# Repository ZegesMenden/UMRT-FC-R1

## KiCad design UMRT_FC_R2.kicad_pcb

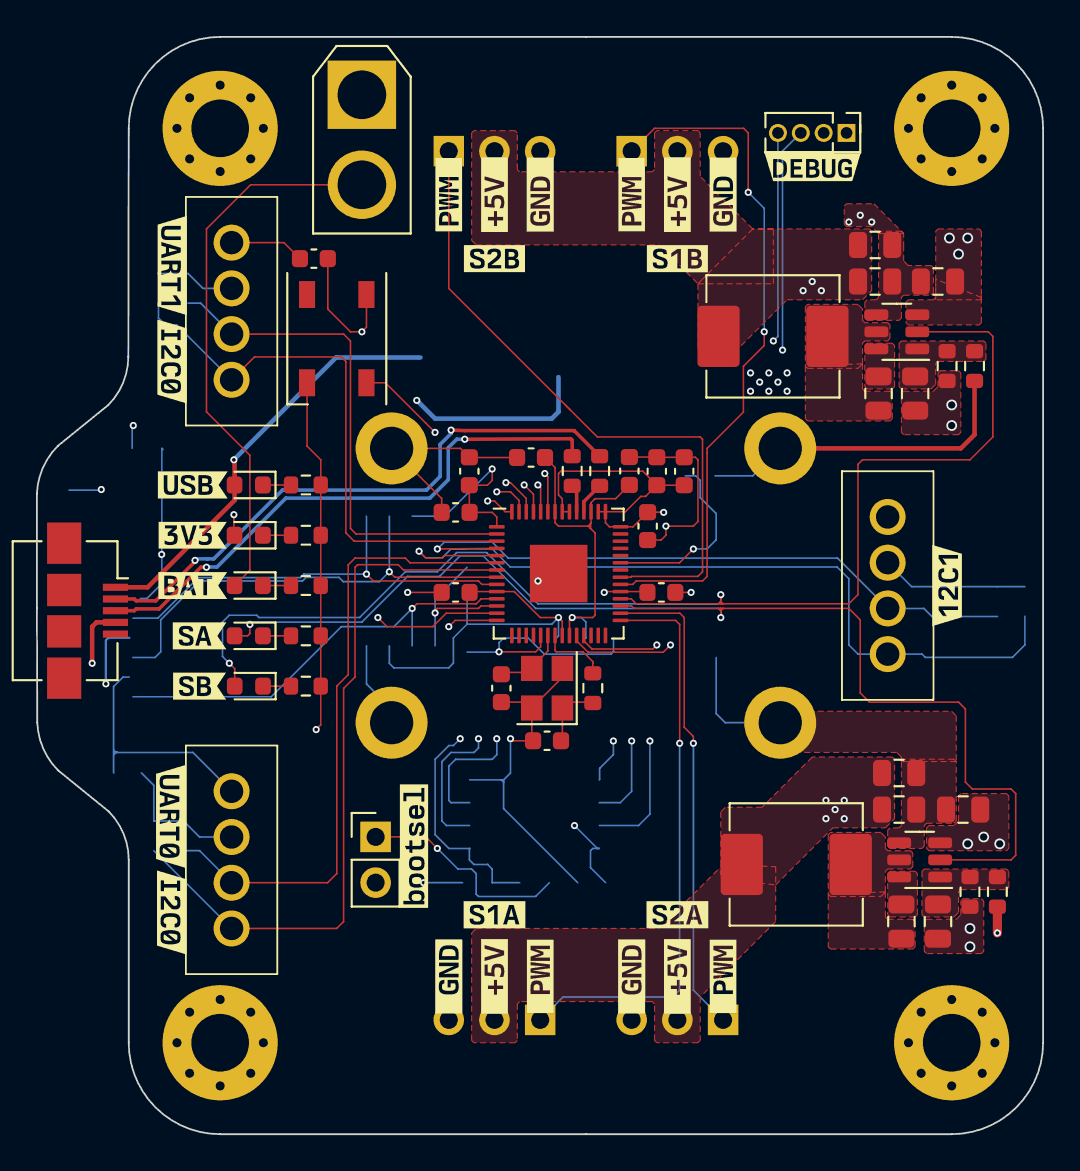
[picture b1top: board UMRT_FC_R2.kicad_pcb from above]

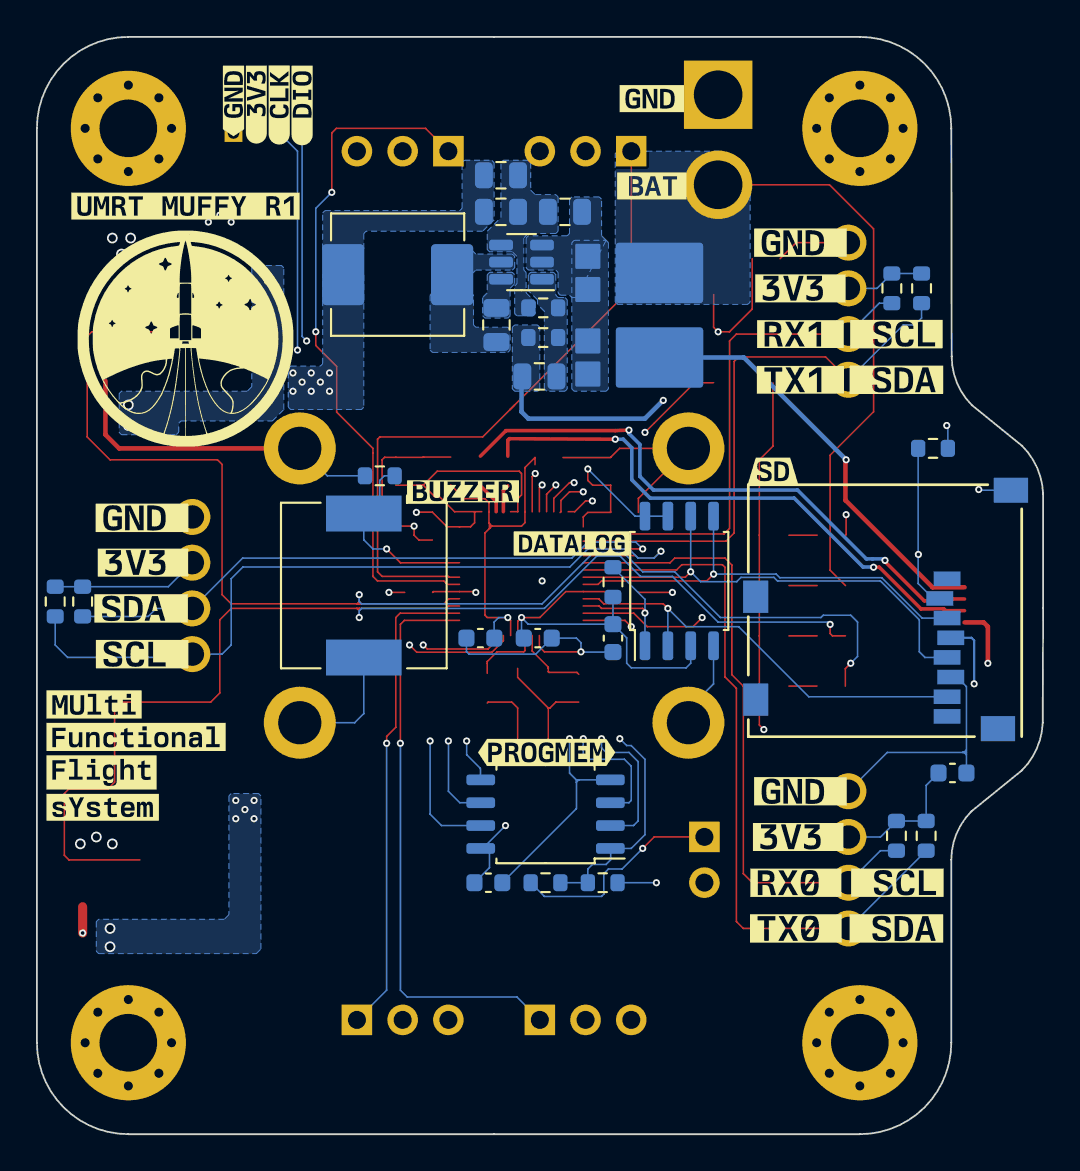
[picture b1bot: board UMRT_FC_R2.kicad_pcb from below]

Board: 4 copper layers, 55.9 x 61.0 mm, 152 parts (62 on the bottom side), 57 nets.

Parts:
BZ1: Buzzer; Buzzer_CUI_CPT-9019S-SMT
C1, C14, C15, C18, C19, C20, C21, C22, C23, C24, C25, C31, C32: 100n; C_0603_1608Metric
C2, C7, C26: 10u; C_0805_2012Metric
C3, C8, C27: 100n; C_0805_2012Metric
C4, C9: 47p; C_0805_2012Metric
C5, C6, C10, C11, C29, C30: 22u; C_0805_2012Metric
C12, C13: 27p; C_0603_1608Metric
C16, C17: 1u; C_0603_1608Metric
C28: 56p; C_0805_2012Metric
D1: WS2812B; LED_WS2812B_PLCC4_5.0x5.0mm_P3.2mm
D2, D3: MBR10; TO-277-D
D4, D5, D6, D7, D8: LED; LED_0603_1608Metric
H1, H2, H3, H4: MountingHole_3.2mm_M3_Pad_Via
J1: USB_A; USB_Micro-B_Amphenol_10104110_Horizontal
J2: Conn_01x02; PinHeader_1x02_P2.54mm_Vertical
J4: Conn_01x02_Pin; AMASS_XT30U-M_1x02_P5.0mm_Vertical
J5, J6, J9, J10: Conn_01x03; PinHeader_1x03_P2.54mm_Horizontal
J7, J8, J11: Conn_01x04_Pin; molex_70543-0038_4pin
J12: Conn_01x04_Pin; PinHeader_1x04_P1.27mm_Vertical
J13: Micro_SD_Card; CONN_3M_2900
L1, L2: 6.8u; L_Abracon_ASPI-0630LR
L3: 4.7u; L_Abracon_ASPI-0630LR
R1, R12, R15, R22: 1k; R_0603_1608Metric
R2, R3, R4, R5, R6, R7, R21, R23, R24, R25: 5k; R_0603_1608Metric
R8, R10: 158k; R_0603_1608Metric
R9, R11, R18: 30.1k; R_0603_1608Metric
R13, R14: 27; R_0603_1608Metric
R16: DNF; R_0603_1608Metric
R17: 93.1k; R_0603_1608Metric
R19, R20: 4.7k; R_0603_1608Metric
U1: adafruit_bno055_nopins
U2, U3, U6: SOT-23-6
U4: RP2040; QFN-56-1EP_7x7mm_P0.4mm_EP3.2x3.2mm
U5: W25Q128JVS; SOIC-8_5.23x5.23mm_P1.27mm
U7: W25Q32JVSS; SOIC-8_5.23x5.23mm_P1.27mm
Y1: Crystal_GND24; Crystal_SMD_3225-4Pin_3.2x2.5mm
kibuzzard-65BFE31C: G***; kibuzzard-65BFE31C
kibuzzard-65BFE313: G***; kibuzzard-65BFE313
kibuzzard-65C2FFB0, kibuzzard-65C2FFB0#2: G***; kibuzzard-65C2FFB0
kibuzzard-65C2FFCF, kibuzzard-65C2FFCF#2: G***; kibuzzard-65C2FFCF
kibuzzard-65C2FFD7, kibuzzard-65C2FFD7#2: G***; kibuzzard-65C2FFD7
kibuzzard-65C300CB: G***; kibuzzard-65C300CB
kibuzzard-65C300CF: G***; kibuzzard-65C300CF
kibuzzard-65C3000E: G***; kibuzzard-65C3000E
kibuzzard-65C3006F: G***; kibuzzard-65C3006F
kibuzzard-65C3007C: G***; kibuzzard-65C3007C
kibuzzard-65C5127A: G***; kibuzzard-65C5127A
kibuzzard-65C30008: G***; kibuzzard-65C30008
kibuzzard-65C30060: G***; kibuzzard-65C30060
kibuzzard-65C30068: G***; kibuzzard-65C30068
kibuzzard-65C30073: G***; kibuzzard-65C30073
kibuzzard-65C30078: G***; kibuzzard-65C30078
kibuzzard-658DCEAA: G***; kibuzzard-658DCEAA
kibuzzard-658DE389: G***; kibuzzard-658DE389
kibuzzard-658DE443: G***; kibuzzard-658DE443
kibuzzard-6590A7CD: G***; kibuzzard-6590A7CD
kibuzzard-6590A8A2: G***; kibuzzard-6590A8A2
kibuzzard-6590A8E1: G***; kibuzzard-6590A8E1
kibuzzard-6590A8E8: G***; kibuzzard-6590A8E8
kibuzzard-6590A8EE: G***; kibuzzard-6590A8EE
kibuzzard-6590A8F4: G***; kibuzzard-6590A8F4
kibuzzard-6590A8F9: G***; kibuzzard-6590A8F9
kibuzzard-6590A70A: G***; kibuzzard-6590A70A
kibuzzard-6590A70E: G***; kibuzzard-6590A70E
kibuzzard-6590A71A: G***; kibuzzard-6590A71A
kibuzzard-6590A84E: G***; kibuzzard-6590A84E
kibuzzard-6590A94C: G***; kibuzzard-6590A94C
kibuzzard-6590A95B: G***; kibuzzard-6590A95B
kibuzzard-6590A703: G***; kibuzzard-6590A703
kibuzzard-6590A840: G***; kibuzzard-6590A840
kibuzzard-6590A898: G***; kibuzzard-6590A898
kibuzzard-6590A900: G***; kibuzzard-6590A900
kibuzzard-6590A950: G***; kibuzzard-6590A950
kibuzzard-6590A956: G***; kibuzzard-6590A956
kibuzzard-6590AA3D: G***; kibuzzard-6590AA3D
kibuzzard-6590AA4E: G***; kibuzzard-6590AA4E
kibuzzard-6590AA5D: G***; kibuzzard-6590AA5D
kibuzzard-6590AA43: G***; kibuzzard-6590AA43
kibuzzard-6590AA49: G***; kibuzzard-6590AA49
kibuzzard-6590AA68: G***; kibuzzard-6590AA68
kibuzzard-6590AB06: G***; kibuzzard-6590AB06
kibuzzard-6590BEFC: G***; kibuzzard-6590BEFC
kibuzzard-6590BF0D: G***; kibuzzard-6590BF0D
kibuzzard-6590BF04: G***; kibuzzard-6590BF04
kibuzzard-6590BF08: G***; kibuzzard-6590BF08
kibuzzard-6591A412: G***; kibuzzard-6591A412
kibuzzard-6591B670: G***; kibuzzard-6591B670
kibuzzard-6591E2EF: G***; kibuzzard-6591E2EF
kibuzzard-6591E33D: G***; kibuzzard-6591E33D
kibuzzard-6591E34D: G***; kibuzzard-6591E34D
kibuzzard-6591E339: G***; kibuzzard-6591E339
kibuzzard-6591E343: G***; kibuzzard-6591E343

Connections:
+1V1: C14.1, C15.1, C16.1, U4.23 (DVDD), U4.45 (VREG_VOUT), U4.50 (DVDD)
+3V3: C1.1, C17.1, C18.1, C19.1, C20.1, C21.1, C22.1, C23.1, C24.1, C25.1, C28.1, C29.1, C30.1, C31.1, C32.2, D1.1 (VDD), D5.2 (A), J7.2, J8.2, J11.2, J12.2, J13.4 (VDD), L3.2, R2.1, R3.1, R4.1, R5.1, R6.1, R7.1, R16.1, R17.1, R19.1, R20.1, U4.1 (IOVDD), U4.10 (IOVDD), U4.22 (IOVDD), U4.33 (IOVDD), U4.42 (IOVDD), U4.43 (ADC_AVDD), U4.44 (VREG_IN), U4.48 (USB_VDD), U4.49 (IOVDD), U5.8 (VCC), U7.3 (IO2), U7.7 (IO3), U7.8 (VCC)
+24V: C2.1, C7.1, D2.2 (A), D4.2 (A), J4.2, U2.3 (VIN), U3.3 (VIN)
/IO/S1A: J5.1, U4.29 (GPIO18)
/IO/S1B: J9.1, U4.34 (GPIO22)
/IO/S2A: J6.1, U4.30 (GPIO19)
/IO/S2B: J10.1, U4.35 (GPIO23)
/IO/SCL0/RX0: J11.4, R3.2, U4.3 (GPIO1)
/IO/SCL0/RX1: J7.4, R5.2, U4.7 (GPIO5)
/IO/SCL1: J8.4, R7.2, U4.5 (GPIO3)
/IO/SDA0/TX0: J11.3, R2.2, U4.2 (GPIO0)
/IO/SDA0/TX1: J7.3, R4.2, U4.6 (GPIO4)
/IO/SDA1: J8.3, R6.2, U4.4 (GPIO2)
/IO/SPWR_A: C4.1, C5.1, C6.1, J5.2, J6.2, L1.2, R8.1
/IO/SPWR_B: C9.1, C10.1, C11.1, J9.2, J10.2, L2.2, R10.1
/IO/SWCLK: J12.3, U4.24 (SWCLK)
/IO/SWDIO: J12.4, U4.25 (SWD)
/RP2040/BUCK_EN_A: D7.2 (A), U2.2 (EN), U4.31 (GPIO20)
/RP2040/BUCK_EN_B: D8.2 (A), U3.2 (EN), U4.32 (GPIO21)
/RP2040/BUZZER: BZ1.1 (-), R1.2, U4.37 (GPIO25)
/RP2040/D+: J1.3 (D+), R13.1
/RP2040/D-: J1.2 (D-), R14.1
/RP2040/NEOPIXEL: D1.4 (DIN), U4.14 (GPIO11)
/RP2040/QSPI_SCLK: U4.52 (QSPI_SCLK), U5.6 (CLK)
/RP2040/QSPI_SD0: U4.53 (QSPI_SD0), U5.5 (DI(IO0))
/RP2040/QSPI_SD1: U4.55 (QSPI_SD1), U5.2 (DO(IO1))
/RP2040/QSPI_SD2: U4.54 (QSPI_SD2), U5.3 (IO2)
/RP2040/QSPI_SD3: U4.51 (QSPI_SD3), U5.7 (IO3)
/RP2040/QSPI_SS: R15.1, R16.2, U4.56 (QSPI_SS), U5.1 (~CS)
/RP2040/SPI_CIPO: J13.7 (DAT0), U4.11 (GPIO8), U7.2 (DO(IO1))
/RP2040/SPI_COPI: J13.3 (CMD), U4.9 (GPIO7), U7.5 (DI(IO0))
/RP2040/SPI_CS_FLASH: R20.2, U4.12 (GPIO9), U7.1 (~CS)
/RP2040/SPI_CS_SD: J13.2 (DAT3/CD), R19.2, U4.13 (GPIO10)
/RP2040/SPI_SCK: J13.5 (CLK), U4.8 (GPIO6), U7.6 (CLK)
/RP2040/XIN: C12.1, U4.20 (XIN), Y1.3
/RP2040/XOUT: R12.1, U4.21 (XOUT)
/RP2040/ucd+: R14.2, U4.46 (USB_DM)
/RP2040/ucd-: R13.2, U4.47 (USB_DP)
GND: BZ1.2 (+), C1.2, C2.2, C5.2, C6.2, C7.2, C10.2, C11.2, C12.2, C13.2, C14.2, C15.2, C16.2, C17.2, C18.2, C19.2, C20.2, C21.2, C22.2, C23.2, C24.2, C25.2, C26.2, C29.2, C30.2, C31.2, C32.1, D1.3 (VSS), H1.1, H2.1, H3.1, H4.1, J1.4 (GND), J2.2, J4.1, J5.3, J6.3, J7.1, J8.1, J9.3, J10.3, J11.1, J12.1, J13.6 (VSS), J13.9 (SHIELD), R1.1, R9.2, R11.2, R18.2, R21.2, R22.2, R23.2, R24.2, R25.2, U1.1 (hole), U2.4 (GND), U3.4 (GND), U4.19 (TESTEN), U4.57 (GND), U5.4 (GND), U6.4 (GND), U7.4 (GND), Y1.2, Y1.4
unnamed: C13.1, R12.2, Y1.1
unnamed: C26.1, D2.1 (K), D3.1 (K), U6.2 (EN), U6.3 (VIN)
unnamed: D4.1 (K), R21.1
unnamed: D5.1 (K), R22.1
unnamed: D6.1 (K), R23.1
unnamed: D7.1 (K), R24.1
unnamed: D8.1 (K), R25.1
unnamed: J2.1, R15.2
unnamed: C3.1, U2.6 (BST)
unnamed: C4.2, R8.2, R9.1, U2.1 (FB)
unnamed: C3.2, L1.1, U2.5 (SW)
unnamed: C8.1, U3.6 (BST)
unnamed: C9.2, R10.2, R11.1, U3.1 (FB)
unnamed: C8.2, L2.1, U3.5 (SW)
unnamed: C27.1, U6.6 (BST)
unnamed: C28.2, R17.2, R18.1, U6.1 (FB)
unnamed: C27.2, L3.1, U6.5 (SW)
VBUS: D3.2 (A), D6.2 (A), J1.1 (VBUS)

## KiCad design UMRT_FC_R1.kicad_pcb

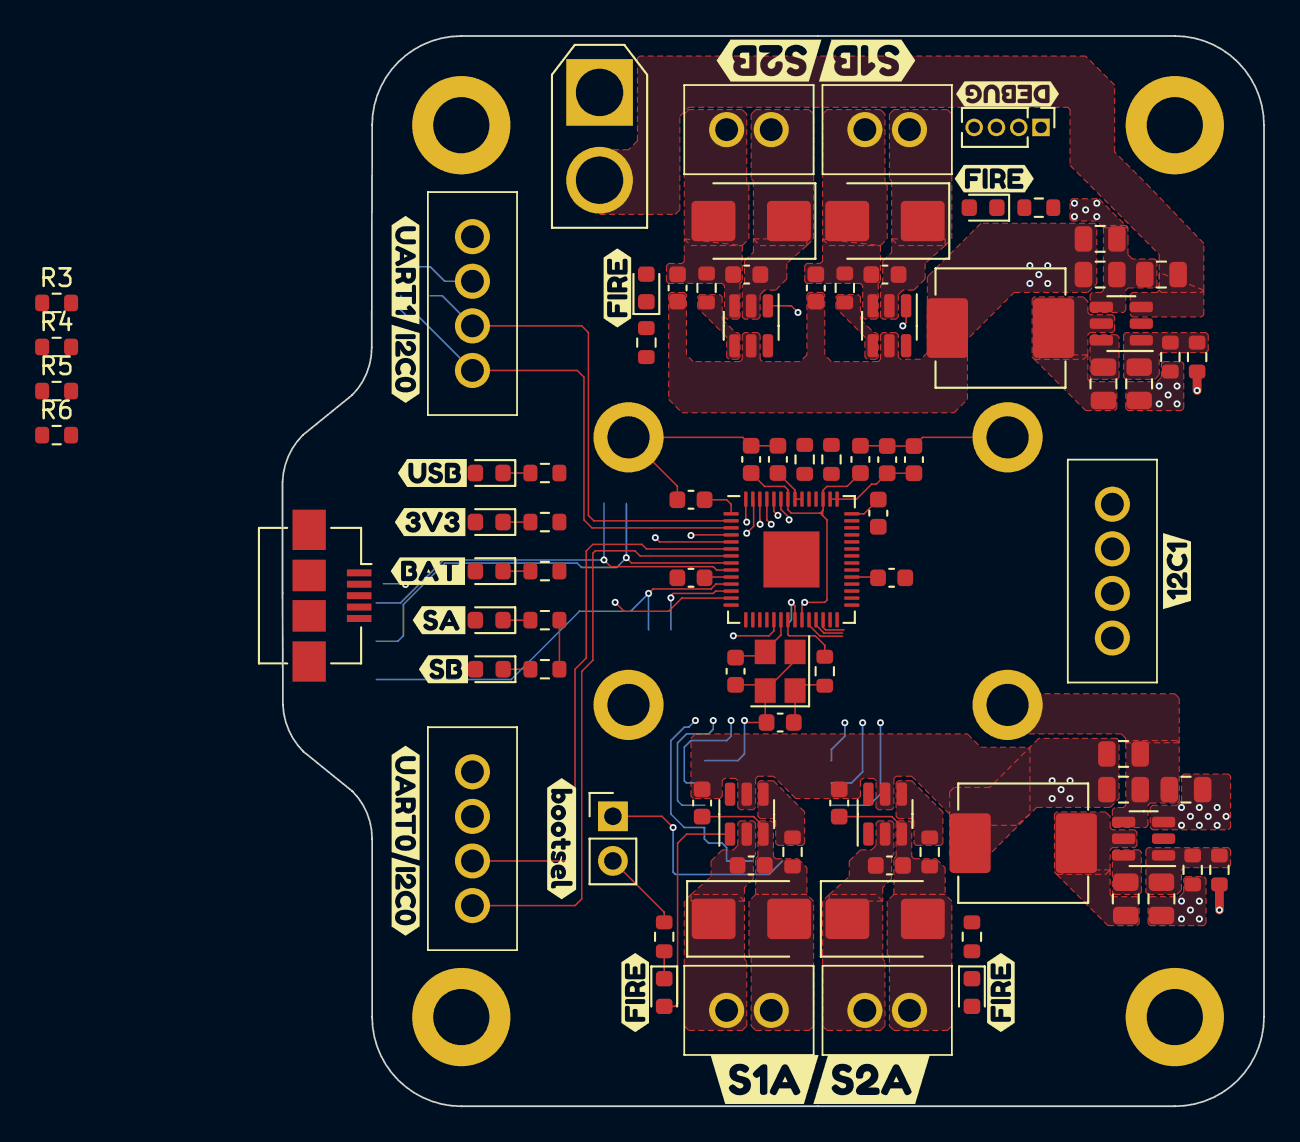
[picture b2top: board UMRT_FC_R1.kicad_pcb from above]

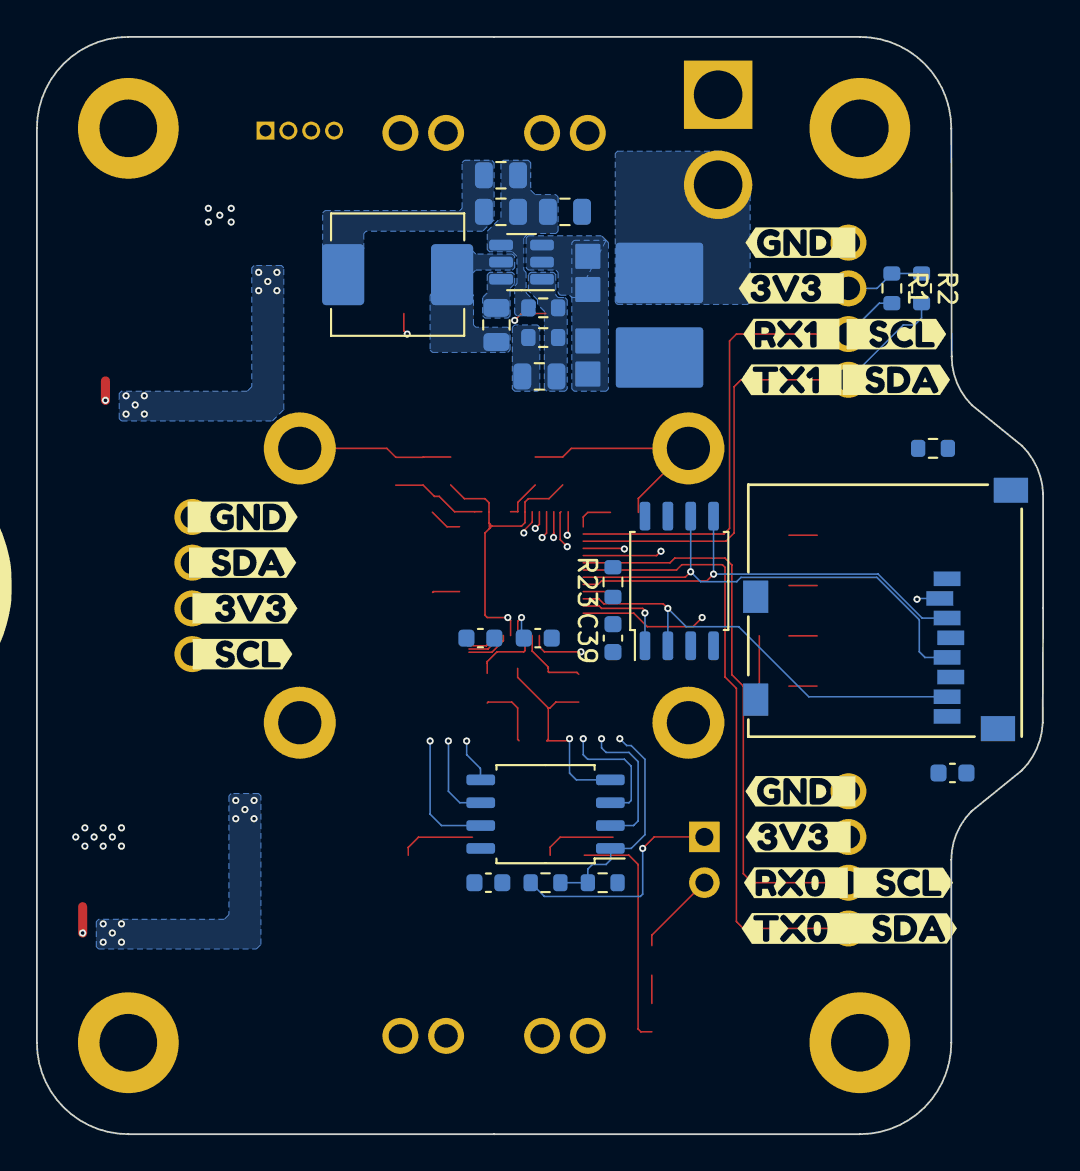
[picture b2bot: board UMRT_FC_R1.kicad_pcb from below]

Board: 4 copper layers, 55.9 x 61.0 mm, 149 parts (41 on the bottom side), 67 nets.

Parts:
C1, C6, C10, C15, C23, C24: 1u; C_0603_1608Metric
C2, C11, C33: 10u; C_0805_2012Metric
C3, C9, C12, C18: 10u; C_0603_1608Metric
C4, C13, C34: 100n; C_0805_2012Metric
C5, C14: 12p; C_0805_2012Metric
C7, C8, C16, C17, C36, C37: 22u; C_0805_2012Metric
C19, C20: 27p; C_0603_1608Metric
C21, C22, C25, C26, C27, C28, C29, C30, C31, C32, C38, C39: 100n; C_0603_1608Metric
C35: 56p; C_0805_2012Metric
D1, D2, D3, D4: S2JTR; D_SMB
D5, D6: MBR10; TO-277-D
D7, D8, D9, D10, D11, D12, D13, D14, D15: LED; LED_0603_1608Metric
J1: USB_A; USB_Micro-B_Amphenol_10104110_Horizontal
J2: Conn_01x02; PinHeader_1x02_P2.54mm_Vertical
J3: Conn_01x02_Pin; AMASS_XT30U-M_1x02_P5.0mm_Vertical
J4, J5, J8, J9: Conn_01x02_Pin; molex_70543-0036_2pin
J6, J7, J10: Conn_01x04_Pin; molex_70543-0038_4pin
J11: Conn_01x04_Pin; PinHeader_1x04_P1.27mm_Vertical
J12: Micro_SD_Card; CONN_3M_2900
L1, L2: 10u; L_Abracon_ASPI-0630LR
L3: 4.7u; L_Abracon_ASPI-0630LR
R1, R2, R3, R4, R5, R6, R24, R26, R27, R28, R29, R30, R31, R32: 5k; R_0603_1608Metric
R7, R10, R11, R14: 473.6; R_0603_1608Metric
R8, R12: 422; R_0603_1608Metric
R9, R13: 30.1; R_0603_1608Metric
R15, R18, R25: 1k; R_0603_1608Metric
R16, R17: 27; R_0603_1608Metric
R19: DNF; R_0603_1608Metric
R20: 93.1k; R_0603_1608Metric
R21: 30.1k; R_0603_1608Metric
R22, R23: 4.7k; R_0603_1608Metric
U1: adafruit_bno055_nopins
U2, U3, U4, U5, U6, U7, U10: SOT-23-6
U8: RP2040; QFN-56-1EP_7x7mm_P0.4mm_EP3.2x3.2mm
U9: W25Q128JVS; SOIC-8_5.23x5.23mm_P1.27mm
U11: W25Q32JVSS; SOIC-8_5.23x5.23mm_P1.27mm
Y1: Crystal_GND24; Crystal_SMD_3225-4Pin_3.2x2.5mm
kibuzzard-658B3C43: G***; kibuzzard-658B3C43
kibuzzard-658B3C48: G***; kibuzzard-658B3C48
kibuzzard-658B3F43: G***; kibuzzard-658B3F43
kibuzzard-658B3F46, kibuzzard-658B3F46#2: G***; kibuzzard-658B3F46
kibuzzard-658B3FA3: G***; kibuzzard-658B3FA3
kibuzzard-658B4089: G***; kibuzzard-658B4089
kibuzzard-658C8ADE: G***; kibuzzard-658C8ADE
kibuzzard-658C8AE5: G***; kibuzzard-658C8AE5
kibuzzard-658C8AED: G***; kibuzzard-658C8AED
kibuzzard-658C8AF6: G***; kibuzzard-658C8AF6
kibuzzard-658C8AFA: G***; kibuzzard-658C8AFA
kibuzzard-658C8B8E, kibuzzard-658C8B8E#2, kibuzzard-658C8B8E#3, kibuzzard-658C8B8E#4: G***; kibuzzard-658C8B8E
kibuzzard-658C8C94, kibuzzard-658C8C94#2, kibuzzard-658C8C94#3: G***; kibuzzard-658C8C94
kibuzzard-658C8CB0, kibuzzard-658C8CB0#2, kibuzzard-658C8CB0#3: G***; kibuzzard-658C8CB0
kibuzzard-658C8CB5: G***; kibuzzard-658C8CB5
kibuzzard-658C8CBA: G***; kibuzzard-658C8CBA
kibuzzard-658C8CF0, kibuzzard-658C8CF0#2: G***; kibuzzard-658C8CF0
kibuzzard-658C8CFC, kibuzzard-658C8CFC#2: G***; kibuzzard-658C8CFC
kibuzzard-658C8D14: G***; kibuzzard-658C8D14
kibuzzard-658C8D18: G***; kibuzzard-658C8D18
kibuzzard-658C97C8: G***; kibuzzard-658C97C8
kibuzzard-658C978A: G***; kibuzzard-658C978A
kibuzzard-658C9743: G***; kibuzzard-658C9743
kibuzzard-658C9748: G***; kibuzzard-658C9748
kibuzzard-658C9778: G***; kibuzzard-658C9778
kibuzzard-658CA21E: G***; kibuzzard-658CA21E

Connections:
+1V1: C21.1, C22.1, C23.1, U8.23 (DVDD), U8.45 (VREG_VOUT), U8.50 (DVDD)
+3V3: C24.1, C25.1, C26.1, C27.1, C28.1, C29.1, C30.1, C31.1, C32.1, C35.1, C36.1, C37.1, C38.1, C39.2, D8.2 (A), J6.2, J7.2, J10.2, J11.2, J12.4 (VDD), L3.2, R1.1, R2.1, R3.1, R4.1, R5.1, R6.1, R19.1, R20.1, R22.1, R23.1, U8.1 (IOVDD), U8.10 (IOVDD), U8.22 (IOVDD), U8.33 (IOVDD), U8.42 (IOVDD), U8.43 (ADC_AVDD), U8.44 (VREG_IN), U8.48 (USB_VDD), U8.49 (IOVDD), U9.8 (VCC), U11.3 (IO2), U11.7 (IO3), U11.8 (VCC)
+24V: C2.1, C11.1, D5.2 (A), D7.2 (A), J3.2, U3.3 (VIN), U6.3 (VIN)
/IO/S1A_P: C3.1, D1.1 (K), J4.1, U2.2 (SOURCE)
/IO/S1B_P: C12.1, D3.1 (K), J9.1, U5.2 (SOURCE)
/IO/S2A_P: C9.1, D2.1 (K), J5.1, U4.2 (SOURCE)
/IO/S2B_P: C18.1, D4.1 (K), J8.1, U7.2 (SOURCE)
/IO/SCL0/RX0: J10.4, R2.2, U8.3 (GPIO1)
/IO/SCL0/RX1: J6.4, R4.2, U8.7 (GPIO5)
/IO/SCL1: J7.4, R6.2, U8.5 (GPIO3)
/IO/SDA0/TX0: J10.3, R1.2, U8.2 (GPIO0)
/IO/SDA0/TX1: J6.3, R3.2, U8.6 (GPIO4)
/IO/SDA1: J7.3, R5.2, U8.4 (GPIO2)
/IO/SWCLK: J11.3, U8.24 (SWCLK)
/IO/SWDIO: J11.4, U8.25 (SWD)
/RP2040/BUCK_EN_A: D10.2 (A), U3.2 (EN), U8.29 (GPIO18)
/RP2040/BUCK_EN_B: D11.2 (A), U6.2 (EN), U8.32 (GPIO21)
/RP2040/D+: J1.3 (D+), R16.1
/RP2040/D-: J1.2 (D-), R17.1
/RP2040/QSPI_SCLK: U8.52 (QSPI_SCLK), U9.6 (CLK)
/RP2040/QSPI_SD0: U8.53 (QSPI_SD0), U9.5 (DI(IO0))
/RP2040/QSPI_SD1: U8.55 (QSPI_SD1), U9.2 (DO(IO1))
/RP2040/QSPI_SD2: U8.54 (QSPI_SD2), U9.3 (IO2)
/RP2040/QSPI_SD3: U8.51 (QSPI_SD3), U9.7 (IO3)
/RP2040/QSPI_SS: R18.1, R19.2, U8.56 (QSPI_SS), U9.1 (~CS)
/RP2040/SOLENOID_1A: D12.2 (A), U2.1 (EN), U8.30 (GPIO19)
/RP2040/SOLENOID_1B: D13.2 (A), U5.1 (EN), U8.34 (GPIO22)
/RP2040/SOLENOID_2A: D14.2 (A), U4.1 (EN), U8.31 (GPIO20)
/RP2040/SOLENOID_2B: D15.2 (A), U7.1 (EN), U8.35 (GPIO23)
/RP2040/SPI_CIPO: J12.7 (DAT0), U8.11 (GPIO8), U11.2 (DO(IO1))
/RP2040/SPI_COPI: J12.3 (CMD), U8.9 (GPIO7), U11.5 (DI(IO0))
/RP2040/SPI_CS_FLASH: R23.2, U8.12 (GPIO9), U11.1 (~CS)
/RP2040/SPI_CS_SD: J12.2 (DAT3/CD), R22.2, U8.13 (GPIO10)
/RP2040/SPI_SCK: J12.5 (CLK), U8.8 (GPIO6), U11.6 (CLK)
/RP2040/XIN: C19.1, U8.20 (XIN), Y1.3
/RP2040/XOUT: R15.1, U8.21 (XOUT)
/RP2040/ucd+: R17.2, U8.46 (USB_DM)
/RP2040/ucd-: R16.2, U8.47 (USB_DP)
/solenoid driver A/SPWR_A: C1.1, C5.1, C6.1, C7.1, C8.1, L1.2, R8.1, U2.5 (VIN), U4.5 (VIN)
/solenoid driver B/SPWR_B: C10.1, C14.1, C15.1, C16.1, C17.1, L2.2, R12.1, U5.5 (VIN), U7.5 (VIN)
GND: C1.2, C2.2, C3.2, C6.2, C7.2, C8.2, C9.2, C10.2, C11.2, C12.2, C15.2, C16.2, C17.2, C18.2, C19.2, C20.2, C21.2, C22.2, C23.2, C24.2, C25.2, C26.2, C27.2, C28.2, C29.2, C30.2, C31.2, C32.2, C33.2, C36.2, C37.2, C38.2, C39.1, D1.2 (A), D2.2 (A), D3.2 (A), D4.2 (A), J1.4 (GND), J2.2, J3.1, J4.2, J5.2, J6.1, J7.1, J8.2, J9.2, J10.1, J11.1, J12.6 (VSS), R7.2, R9.2, R10.2, R11.2, R13.2, R14.2, R21.2, R24.2, R25.2, R26.2, R27.2, R28.2, R29.2, R30.2, R31.2, R32.2, U1.1 (hole), U2.3 (GND), U3.4 (GND), U4.3 (GND), U5.3 (GND), U6.4 (GND), U7.3 (GND), U8.19 (TESTEN), U8.57 (GND), U9.4 (GND), U10.4 (GND), U11.4 (GND), Y1.2, Y1.4
unnamed: C20.1, R15.2, Y1.1
unnamed: C33.1, D5.1 (K), D6.1 (K), U10.2 (EN), U10.3 (VIN)
unnamed: D7.1 (K), R24.1
unnamed: D8.1 (K), R25.1
unnamed: D9.1 (K), R26.1
unnamed: D10.1 (K), R27.1
unnamed: D11.1 (K), R28.1
unnamed: D12.1 (K), R29.1
unnamed: D13.1 (K), R30.1
unnamed: D14.1 (K), R31.1
unnamed: D15.1 (K), R32.1
unnamed: J2.1, R18.2
unnamed: R7.1, U2.4 (ILIMIT)
unnamed: C4.1, U3.6 (BST)
unnamed: C5.2, R8.2, R9.1, U3.1 (FB)
unnamed: C4.2, L1.1, U3.5 (SW)
unnamed: R10.1, U4.4 (ILIMIT)
unnamed: R11.1, U5.4 (ILIMIT)
unnamed: C13.1, U6.6 (BST)
unnamed: C14.2, R12.2, R13.1, U6.1 (FB)
unnamed: C13.2, L2.1, U6.5 (SW)
unnamed: R14.1, U7.4 (ILIMIT)
unnamed: C34.1, U10.6 (BST)
unnamed: C35.2, R20.2, R21.1, U10.1 (FB)
unnamed: C34.2, L3.1, U10.5 (SW)
VBUS: D6.2 (A), D9.2 (A), J1.1 (VBUS)

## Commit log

2023-11-27 added some notes and PDF
2023-12-27 started on layout and added SD/flash/BNO
2024-02-20 final
